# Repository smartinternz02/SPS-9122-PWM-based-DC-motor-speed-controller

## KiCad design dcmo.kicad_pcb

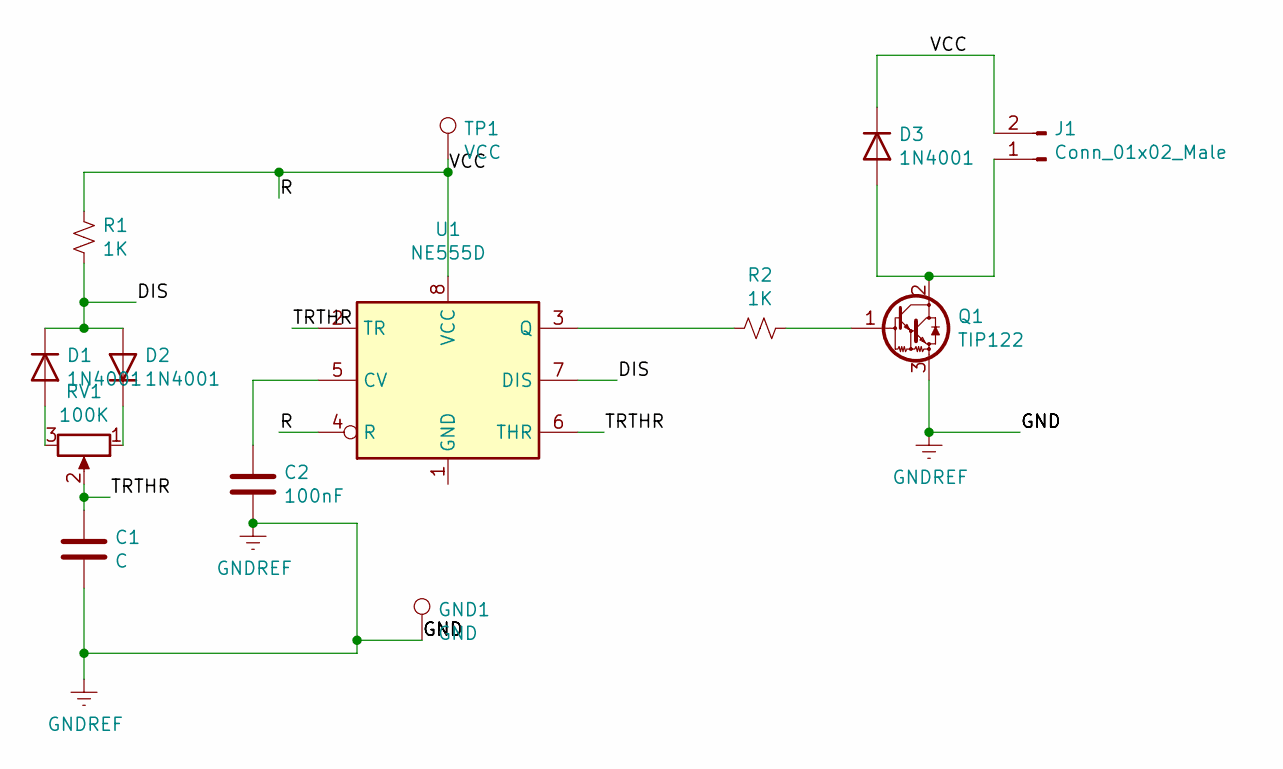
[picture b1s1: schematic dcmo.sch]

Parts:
C1: C; C_1206_3216Metric
C2: 100nF; C_1206_3216Metric
D1, D2, D3: 1N4001; D_DO-41_SOD81_P10.16mm_Horizontal
GND1: GND; TestPoint_Pad_D4.0mm
J1: Conn_01x02_Male; SolderWire-0.1sqmm_1x02_P3.6mm_D0.4mm_OD1mm
Q1: TIP122; TO-220-3_Vertical
R1, R2: 1K; R_1206_3216Metric
RV1: 100K; Potentiometer_ACP_CA9-VSMD_Vertical
TP1: VCC; TestPoint_Pad_D4.0mm
U1: NE555D; SOIC-8_3.9x4.9mm_P1.27mm

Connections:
/DIS: D1.1 (K), D2.2 (A), R1.2, U1.7 (DIS)
/R: D3.1 (K), J1.2, R1.1, TP1.1, U1.4 (R), U1.8 (VCC)
/TRTHR: C1.1, RV1.2, U1.2 (TR), U1.6 (THR)
GNDREF: C1.2, C2.2, GND1.1, Q1.3 (E); also elsewhere on the board
unnamed: C2.1, U1.5 (CV)
unnamed: D1.2 (A), RV1.3
unnamed: D2.1 (K), RV1.1
unnamed: D3.2 (A), J1.1, Q1.2 (C)
unnamed: Q1.1 (B), R2.1
unnamed: R2.2, U1.3 (Q)

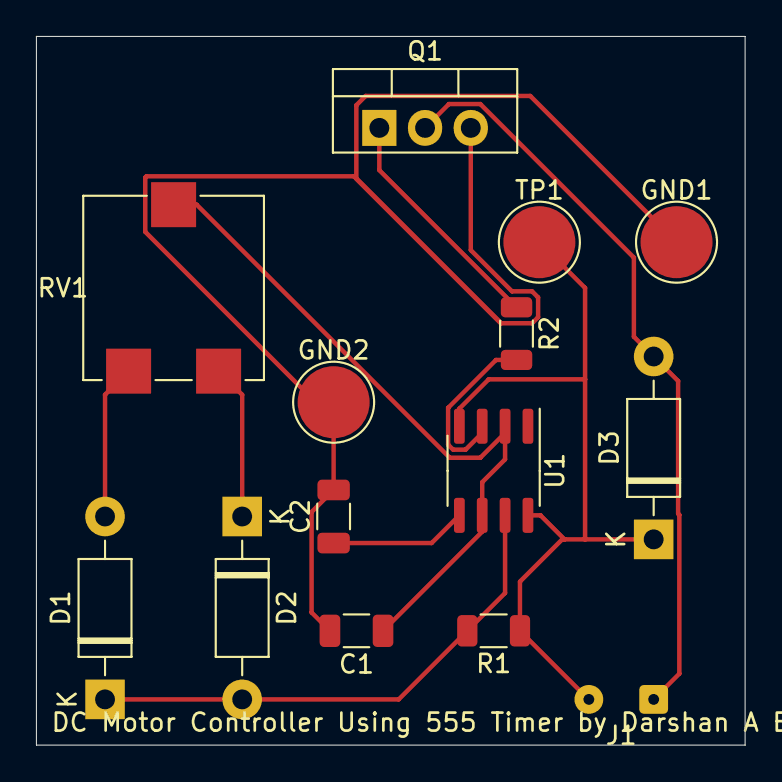
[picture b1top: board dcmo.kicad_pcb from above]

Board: 2 copper layers, 39.4 x 39.4 mm, 14 parts (0 on the bottom side), 10 nets.

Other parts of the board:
GND2: GND; TestPoint_Pad_D4.0mm

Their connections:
GNDREF: GND2.1; also elsewhere on the board

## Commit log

2021-03-24 Create DCMotor Controller using 555 Timer
